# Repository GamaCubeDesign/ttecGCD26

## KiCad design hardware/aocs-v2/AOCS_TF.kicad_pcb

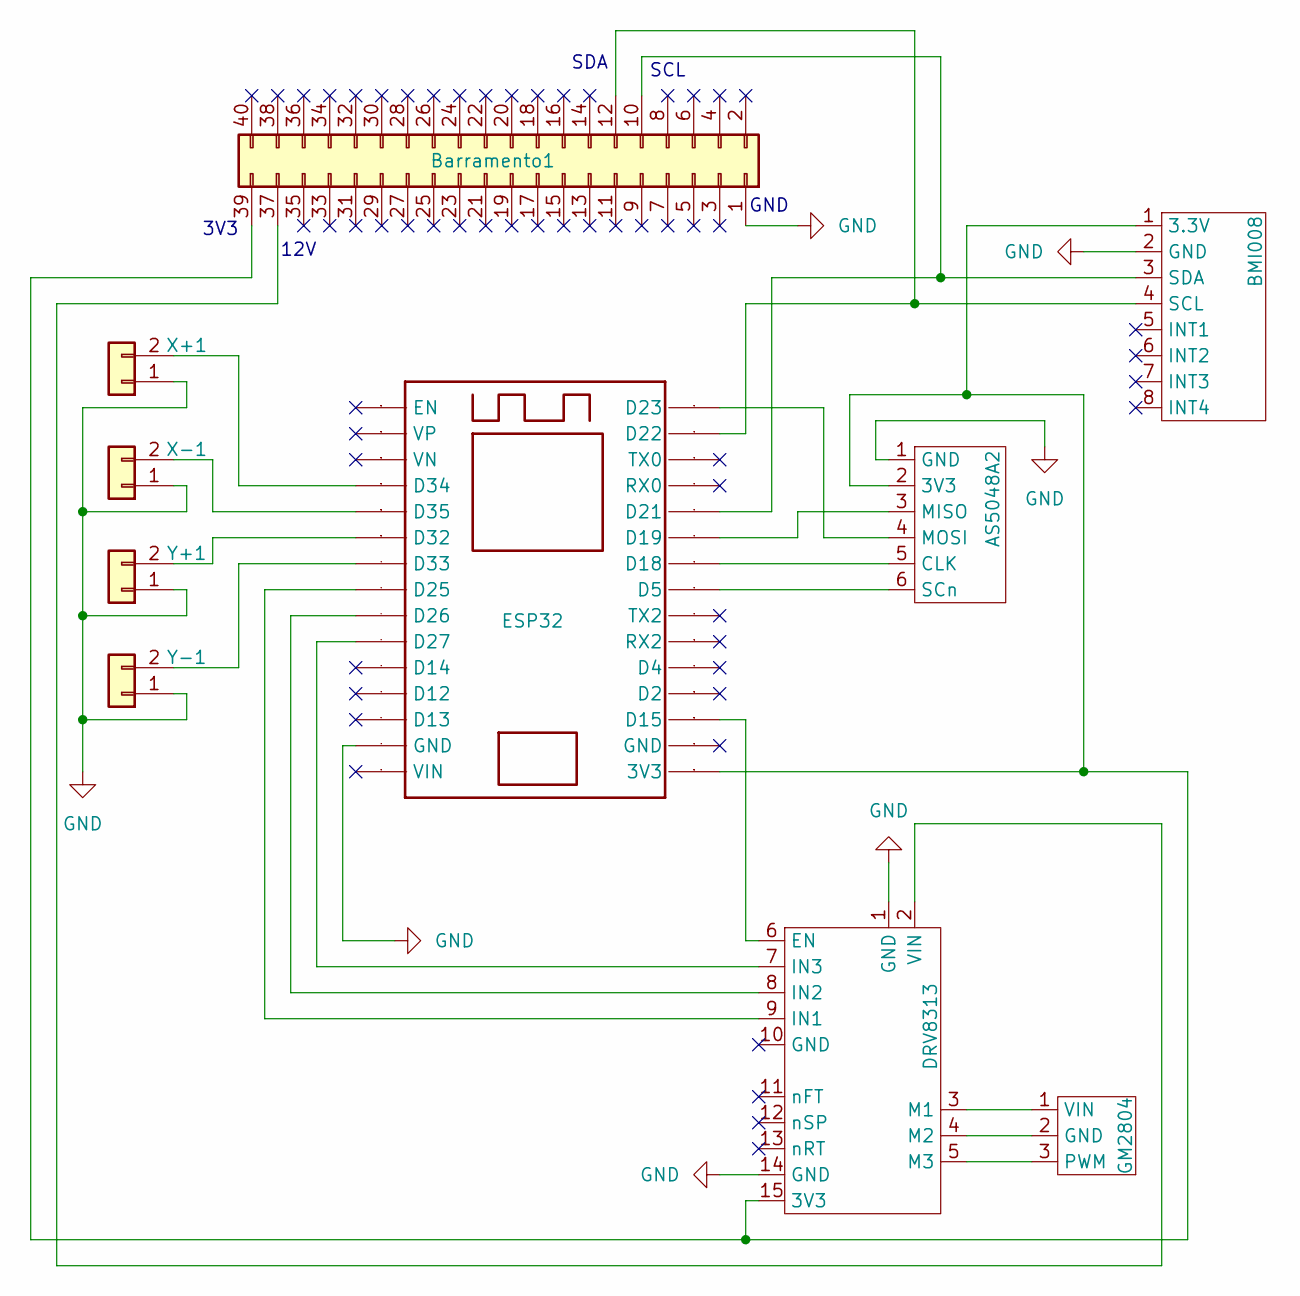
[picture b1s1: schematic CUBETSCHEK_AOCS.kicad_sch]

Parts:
AS5048A2: AS5048A
BMI008: BMI088
Barramento1: Barramento
DRV8313: DRV8313; DRV3813
ESP32: ESP32; ESP32-30p
GM2804: GM2804; GM2804_Molex_KK-3p-254
X+1: JST; JST_PLACA
X-1: JST; JST_PLACA
Y+1: JST; JST_PLACA
Y-1: JST; JST_PLACA

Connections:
GND: AS5048A2.1 (GND), BMI008.2 (GND), Barramento1.1, DRV8313.1 (GND), DRV8313.14 (GND), ESP32.2 (GND), X+1.1, X-1.1, Y+1.1, Y-1.1
unnamed: AS5048A2.2 (3V3), BMI008.1 (3.3V), Barramento1.39, DRV8313.15 (3V3), ESP32.16 (3V3)
unnamed: AS5048A2.5 (CLK), ESP32.24 (D18)
unnamed: AS5048A2.3 (MISO), ESP32.25 (D19)
unnamed: AS5048A2.4 (MOSI), ESP32.30 (D23)
unnamed: AS5048A2.6 (SCn), ESP32.23 (D5)
unnamed: BMI008.4 (SCL), Barramento1.12, ESP32.29 (D22)
unnamed: BMI008.3 (SDA), Barramento1.10, ESP32.26 (D21)
unnamed: Barramento1.37, DRV8313.2 (VIN)
unnamed: DRV8313.6 (EN), ESP32.18 (D15)
unnamed: DRV8313.9 (IN1), ESP32.8 (D25)
unnamed: DRV8313.8 (IN2), ESP32.7 (D26)
unnamed: DRV8313.7 (IN3), ESP32.6 (D27)
unnamed: DRV8313.3 (M1), GM2804.1 (VIN)
unnamed: DRV8313.4 (M2), GM2804.2 (GND)
unnamed: DRV8313.5 (M3), GM2804.3 (PWM)
unnamed: ESP32.10 (D32), Y+1.2
unnamed: ESP32.9 (D33), Y-1.2
unnamed: ESP32.12 (D34), X+1.2
unnamed: ESP32.11 (D35), X-1.2

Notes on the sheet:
GND
SDA
SCL
3V3
12V

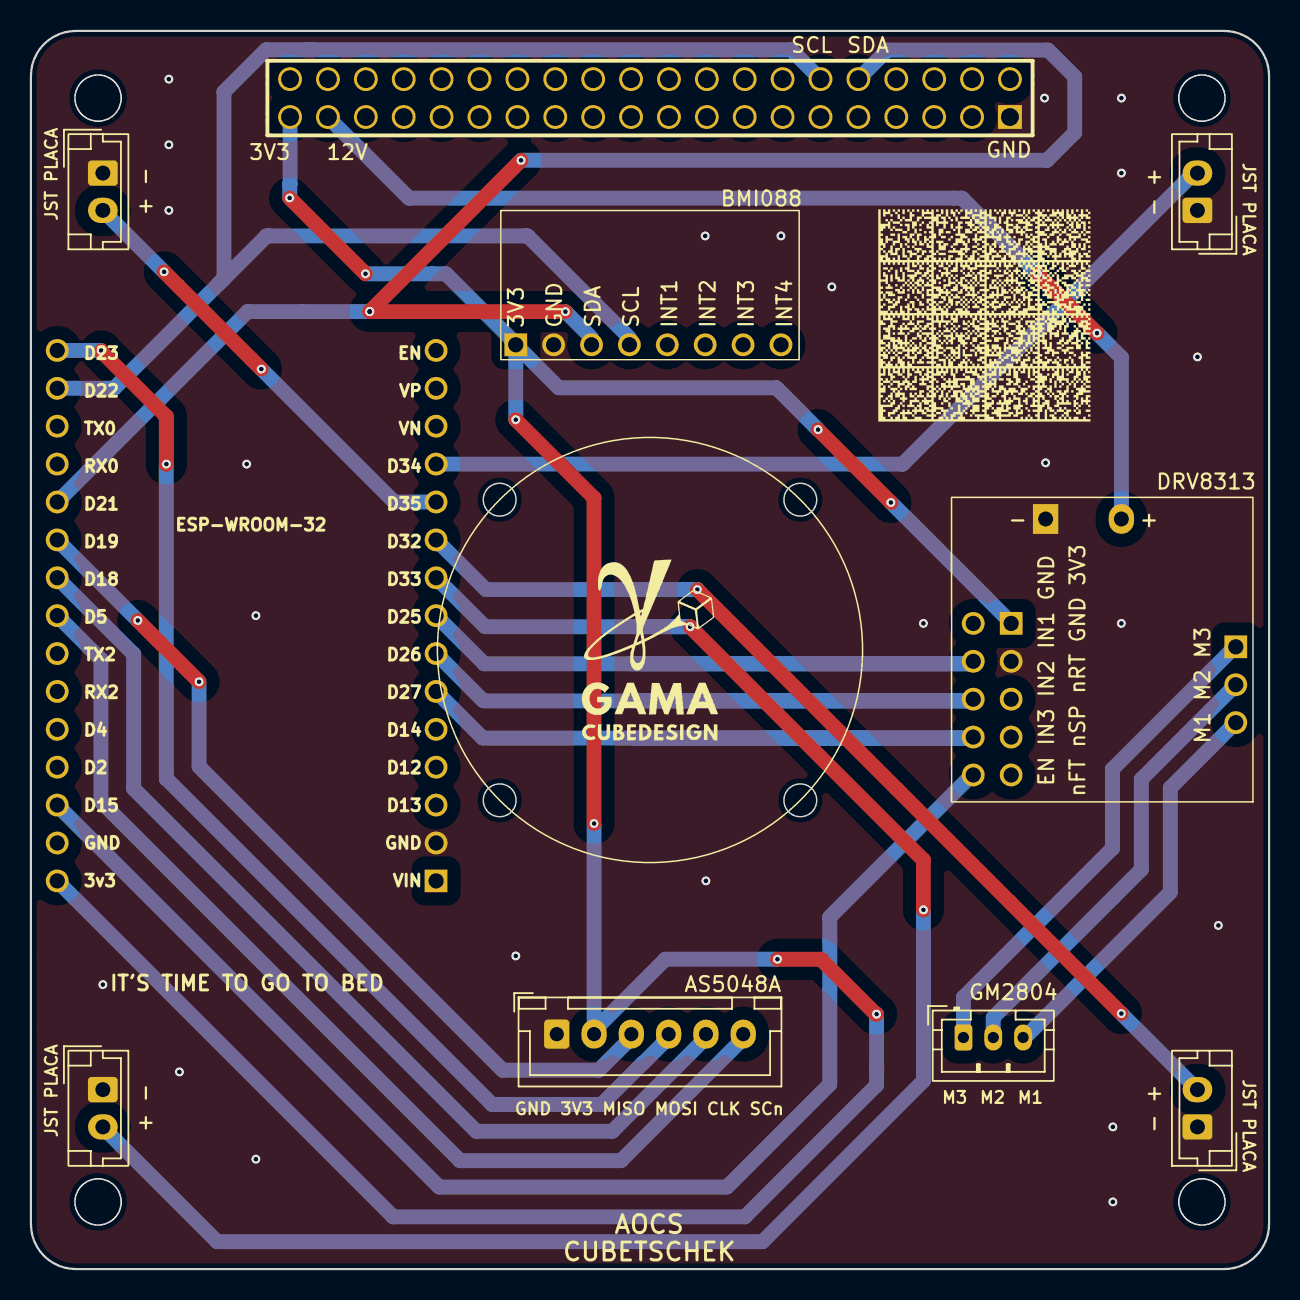
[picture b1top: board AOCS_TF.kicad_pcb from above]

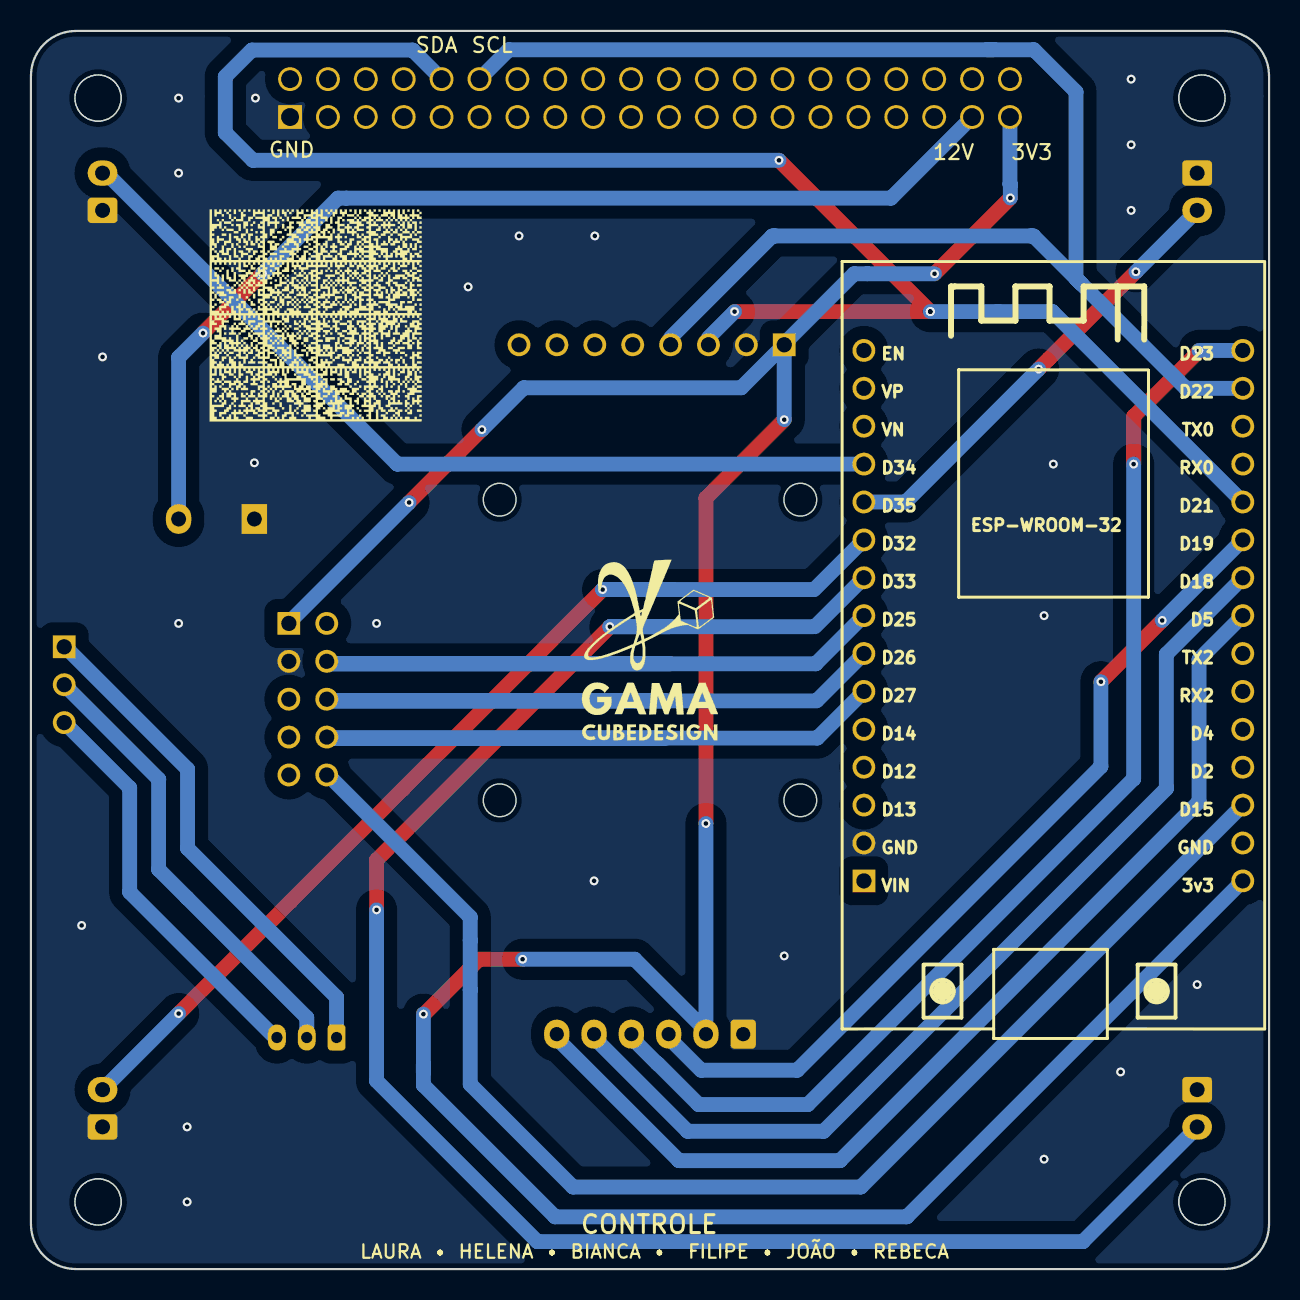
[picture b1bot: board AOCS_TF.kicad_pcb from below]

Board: 2 copper layers, 83.0 x 83.0 mm, 12 parts (2 on the bottom side), 20 nets.

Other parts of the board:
logo: LOGO; logo
logo#2: LOGO; logo

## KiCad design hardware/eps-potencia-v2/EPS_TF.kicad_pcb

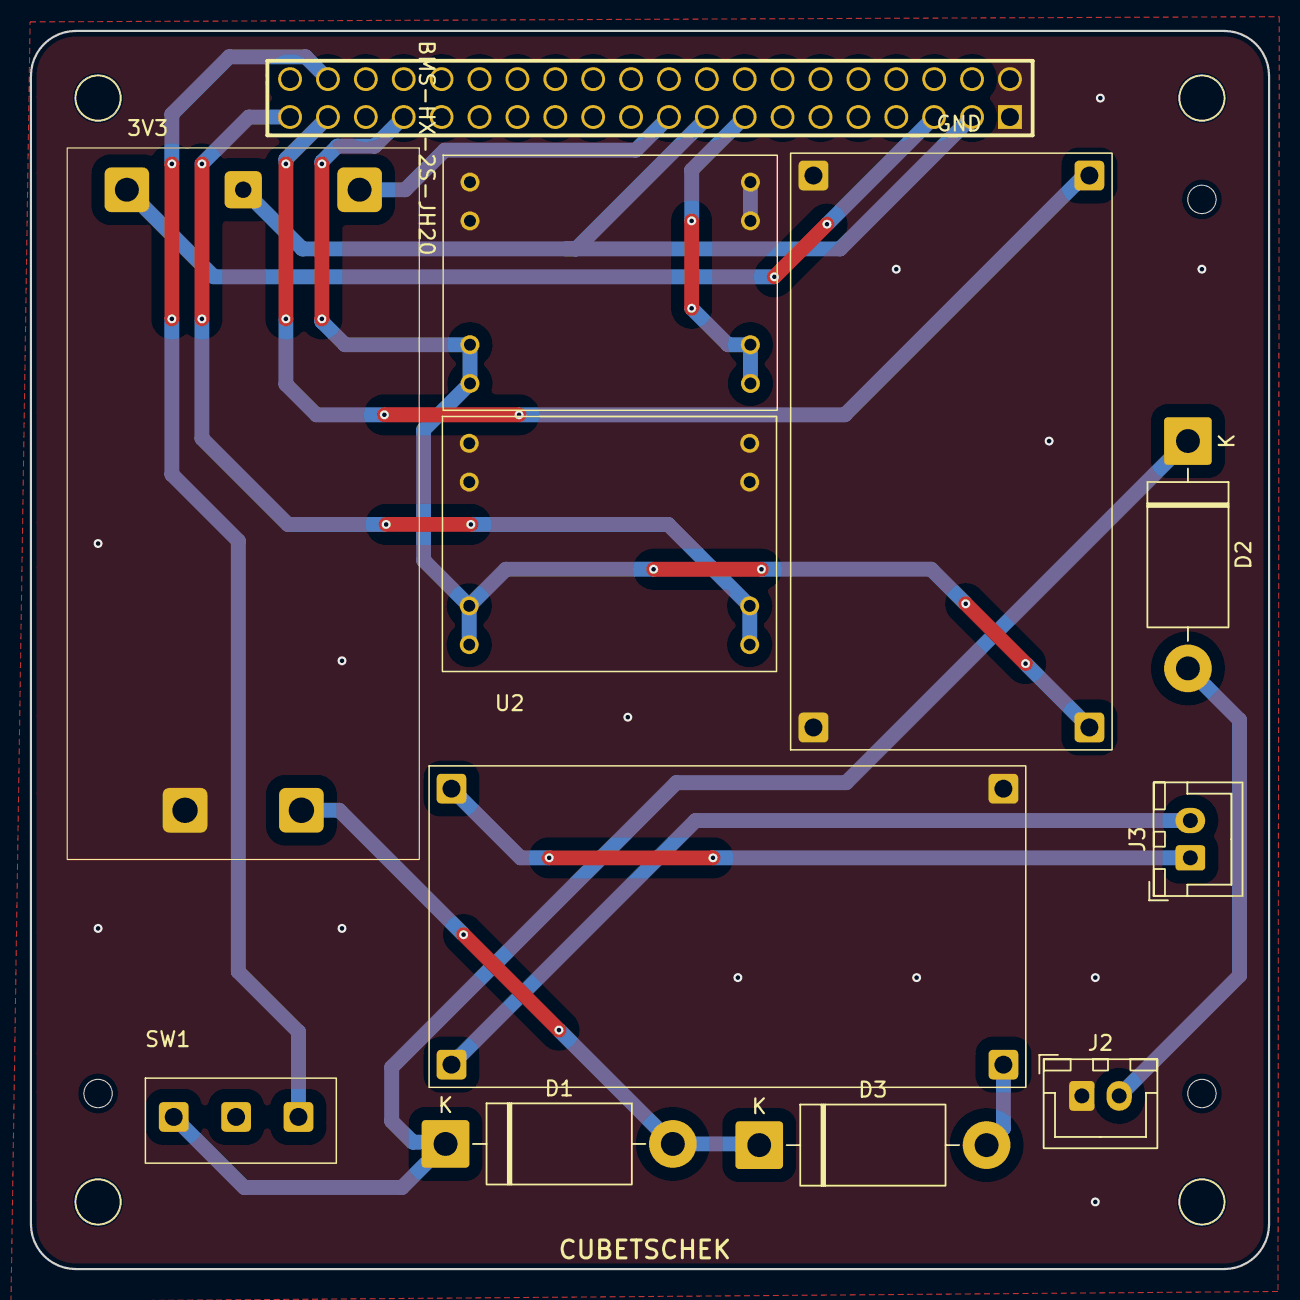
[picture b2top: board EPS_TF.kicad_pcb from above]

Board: 2 copper layers, 83.0 x 83.0 mm, 12 parts (0 on the bottom side), 15 nets.

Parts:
BMS-HX-2S-JH20: HX-2S-JH20
D1, D2, D3: 1N5822; D_DO-201AD_P15.24mm_Horizontal
J1: Conn_02x20_Odd_Even; PC104_PSTD-2.54-2X20P
J2, J3: Conn_01x02_Pin; JST_XH_B2B-XH-A_1x02_P2.50mm_Vertical
MP1584_Module1, MP1584_Module2: MP1584_MODULE
SW1: SW_SPDT; KW10
U1, U2: TPS61088

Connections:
/3V3: J1.39, MP1584_Module2.4 (VOUT+)
/5V: J1.15, MP1584_Module1.4 (VOUT+)
/8V(Bruto): J1.38, SW1.1 (A)
/8V(Liq): J1.33, MP1584_Module1.1 (VIN+), MP1584_Module2.1 (VIN+), U1.1 (VIN+)
/12V: J1.37, U1.4 (VOUT+)
/GND: BMS-HX-2S-JH20.5 (P-), J1.1, J1.2, J2.1, MP1584_Module1.2 (VIN-), MP1584_Module1.3 (VOUT-), MP1584_Module2.2 (VIN-), MP1584_Module2.3 (VOUT-), U1.2 (VIN-), U1.3 (VOUT-), U2.3 (VOUT-)
/Negativo Bateria Inf: BMS-HX-2S-JH20.3 (B-), J1.5
/Negativo Bateria Sup: BMS-HX-2S-JH20.2 (BM), J1.3, J1.17
/Positivo Bateria Sup: BMS-HX-2S-JH20.1 (B+), J1.19
unnamed: BMS-HX-2S-JH20.4 (P+), D1.2 (A), D3.1 (K)
unnamed: D1.1 (K), D2.1 (K), SW1.3 (C)
unnamed: D2.2 (A), J2.2
unnamed: D3.2 (A), U2.4 (VOUT+)
unnamed: J3.1, U2.2 (VIN-)
unnamed: J3.2, U2.1 (VIN+)
